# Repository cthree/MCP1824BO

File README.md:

# MCP1824-ADJ 0.8V-4.5V 300mA LDO Breakout Board

A small breakout board for the MCP1824-ADJ Adjustable LDO from Microchip designed
to deliver 300mA at voltages ranging from 0.8V to 4.5V from its fused USB Micro B
jack. It is laid out to provide power rails to a standard solderless breadboard
with the following characteristics:

* 1A @ 5V fused and clamped (1.8A & 5.1V) direct from the USB Micro B input jack,
* 300mA @ 0.8-4.5V from the MCP1824-ADJ LDO.

You can [order this board](https://oshpark.com/shared_projects/W8U1qi3h) ready made
from oshpark.com. It's 1 sq. in. so it will cost $5 for 3.

I use these to prototype new projects needing an LDO. Feel free to do the same.
I designed this to be easy to hand solder.

The passives are all 0603 ERJ-3GEYJxxx Panasonic resistors and GRM188xxxxxx
capacitors from muRata. See the BOM for a complete parts list. Everything is
available from Digikey.

There is a jumper (Rev A) or switch (Rev B) to toggle the SHDN control of the
MCP1824-ADJ. An LED on each power rail indicates live power to that rail. The
grounds are all connected at USB potential.

## About the MCP1824-ADJ LDO Linear Voltage Regulator

The [Datasheet](http://ww1.microchip.com/downloads/en/DeviceDoc/22070a.pdf)
is your primary reference.

The MCP1824/MCP1824S is a 300 mA Low Dropout (LDO) linear regulator that provides
high current and low output voltages. The MCP1824 comes in a fixed or
adjustable output voltage version, with an output voltage range of 0.8V to 5.0V.
The 300 mA output current capability, combined with the low output voltage
capability, make the MCP1824 a good choice for new sub-1.8V output voltage LDO
applications that have high current demands.

### Features

* 300 mA Output Current Capability
* Input Operating Voltage Range: 2.1V to 6.0V
* Adjustable Output Voltage Range: 0.8V to 5.0V
* Low Dropout Voltage: 200 mV Typical at 300 mA
* Typical Output Voltage Tolerance: 0.4%
* Stable with 1.0 µF Ceramic Output Capacitor
* Fast Response to Load Transients
* Low Supply Current: 120 µA (typical)
* Low Shutdown Supply Current: 0.1 µA (typical)
* Fixed Delay on Power Good Output
* Short Circuit Current Limiting and Over-temperature Protection
* 5-Lead Plastic SOT-223, SOT-23 Package

## Bugs, Issues and Contributions

If you discover any issues with it or the parts used please let me know by opening
an issue or forking the repo and submitting a pull request with your fix.

Happy hacking!

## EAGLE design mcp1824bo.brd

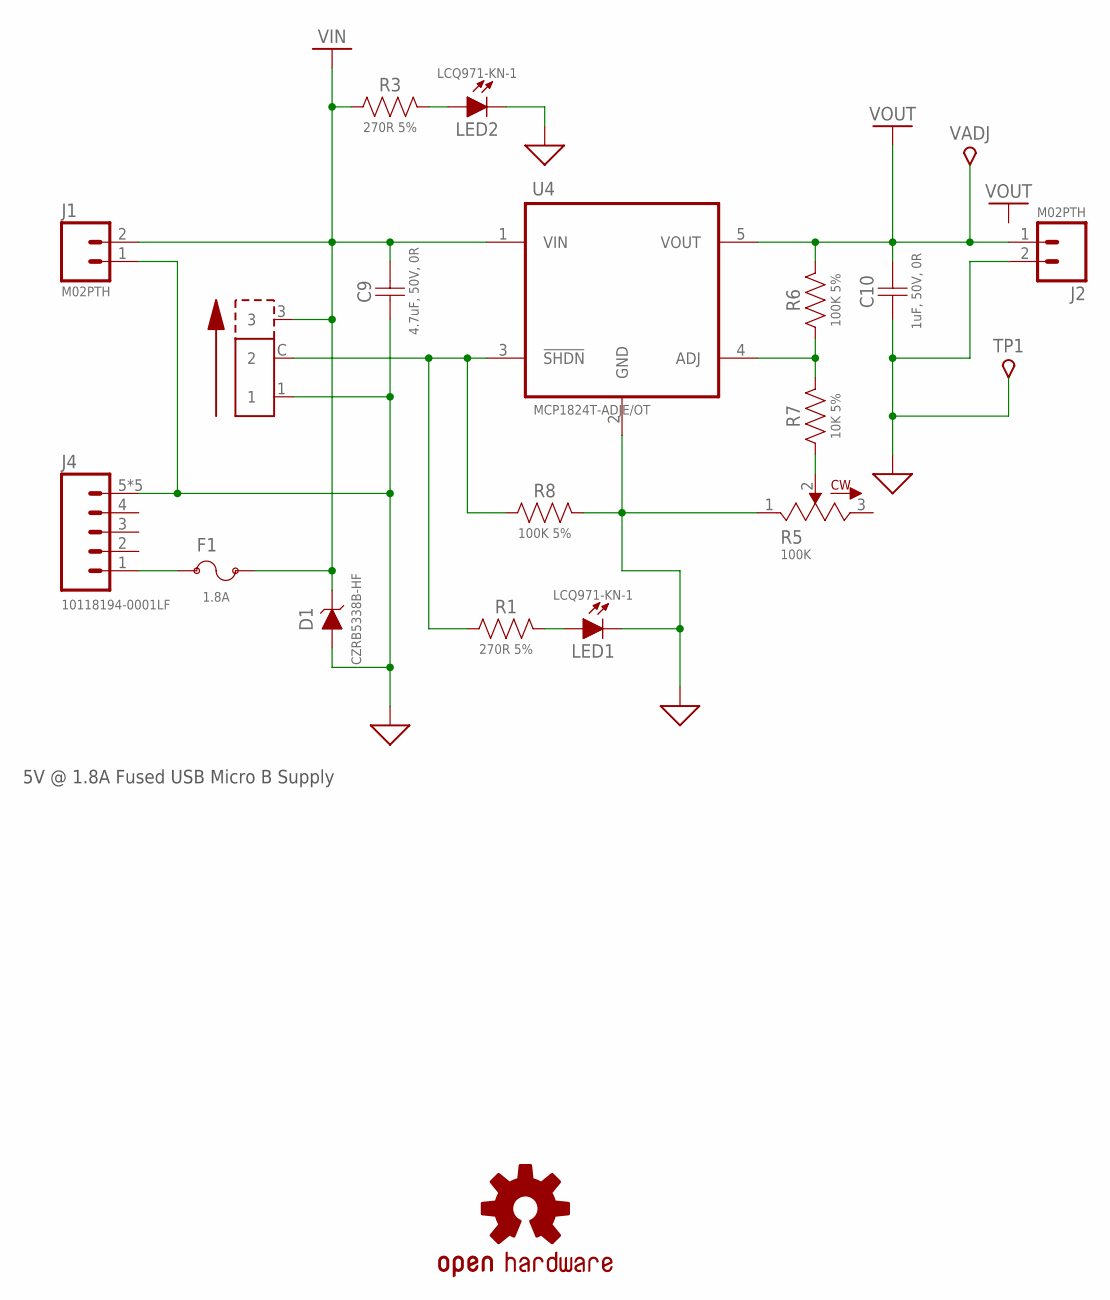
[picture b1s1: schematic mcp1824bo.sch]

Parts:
C9: 4.7uF, 50V, 0R; 31-1206
C10: 1uF, 50V, 0R; 21-0805
D1: CZRB5338B-HF; DO-214AA
F1: 1.8A; 1206
J1, J2: M02PTH; 1X02
J4: 10118194-0001LF; USB-MICROB
LED1, LED2: LCQ971-KN-1; CHIPLED_0603
LOGO1: OSHW-LOGOS; OSHW-LOGO-S
R1, R3: 270R 5%; R0603
R5: 100K; T93YA
R6, R8: 100K 5%; R0603
R7: 10K 5%; R0603
SW1: CL-SB-12A-01; CL-SB-12A
TP1: TP-5001K-040; TP5000K-040
U4: MCP1824T-ADJE/OT; SOT95P270X145-5N
VADJ: TP-5000K-040; TP5000K-040

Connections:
ADJ: R6.1, R7.2, U4.4 (ADJ)
ADJ2: R5.2, R7.1
GND: C9.1, C10.1, D1.A, J1.1, J2.2, J4.5, J4.6 (5), J4.7 (5), J4.8 (5), J4.9 (5), LED1.C, LED2.C, R5.1, R8.2, SW1.1, TP1.PP, U4.2 (GND)
LED1: LED1.A, R1.2
LED2: LED2.A, R3.2
SHDN: R1.1, R8.1, SW1.C (2), U4.3 (!SHDN)
VIN: C9.2, D1.C, F1.2, J1.2, R3.1, SW1.3, U4.1 (VIN)
VOUT: C10.2, J2.1, R6.2, U4.5 (VOUT), VADJ.PP
VUSB: F1.1, J4.1

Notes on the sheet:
5V @ 1.8A Fused USB Micro B Supply

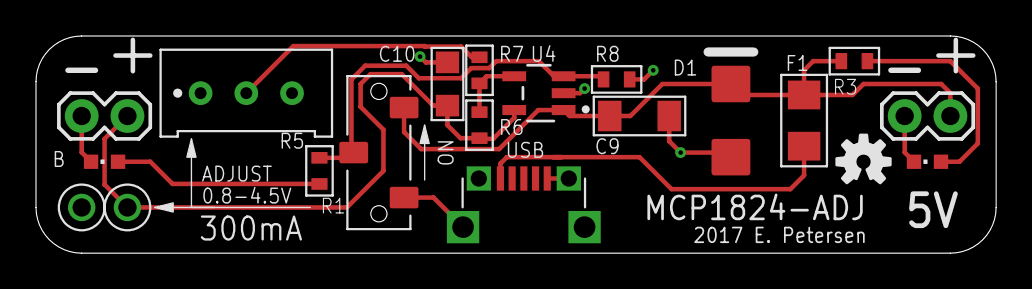
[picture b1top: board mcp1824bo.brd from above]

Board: 2 copper layers, 53.3 x 12.1 mm, 20 parts (0 on the bottom side), 9 nets.

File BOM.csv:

"Part","Value","Device","Package","Description"
"C9","4.7uF, 50V","GRM31CR71H475KA12L","1206","Murata SMD Ceramic Capacitor"
"C10","1uF, 50V","GRM21BR71H105KA12L","0805","Murata SMD Ceramic Capacitor"
"D1","5.1V, 5W","CZRB5338B-HF","DO-214AA","Comchip SMD Zener Diode"
"F1","1.0A HOLD, 1.8A TRIP","1206L100","1206","Littelfuse POLYFUSE® Resettable PTC"
"J1","M02PTH","M02PTH","1X02","Standard 2-pin 0.1" header"
"J2","M02PTH","M02PTH","1X02","Standard 2-pin 0.1" header"
"J3","M02PTH","M02PTH","1X02","Standard 2-pin 0.1" header"
"J4","USB Micro B","10118194-0001LF","USB-MICROB","Amphenol USB Micro B Board Connector"
"LED1","2.2Vf, 25mA, Green","LCQ971-KN-1","0603","OMRON SMD LED"
"LED2","2.2Vf, 25mA, Green","LCQ971-KN-1","0603","OMRON SMD LED"
"R1","270R 5%","ERJ-3GEYJ271","0603","Panasonic ERJ Thick Film Chip Resistor"
"R3","270R 5%","ERJ-3GEYJ271","0603","Panasonic ERJ Thick Film Chip Resistor"
"R5","100K","T93YA104KT20","T93YA","VISHAY T93 Series Cermet Style Trimmer Potentiometers"
"R6","100K 5%","ERJ-3GEYJ104","0603","Panasonic ERJ Thick Film Chip Resistor"
"R7","10K 5%","ERJ-3GEYJ103","0603","Panasonic ERJ Thick Film Chip Resistor"
"R8","100K 5%","ERJ-3GEYJ104","0603","Panasonic ERJ Thick Film Chip Resistor"
"TP1","Black Compact","TP-5001K-040","TP5000K-040","Keystone 5000 Series Test Points"
"TP2","Red Compact","TP-5000K-040","TP5000K-040","Keystone 5000 Series Test Points"
"U4","300mA, 200mV DO","MCP1824T-ADJE/OT","SOT23-5","Microchip Low Quiescent Current LDO Regulator"

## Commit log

2017-04-19 replace SHDN jumper with a slide switch
